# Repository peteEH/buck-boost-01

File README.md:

# buck-boost-01
buck boost programmable regulator - breakout board

- programmable (i2c) buck-boost converter
- 22V in MAX / 20V out MAX - up to 3A out / 4A in
- intention to use as a serially controlled battery charger
- breakout board for the mp28167

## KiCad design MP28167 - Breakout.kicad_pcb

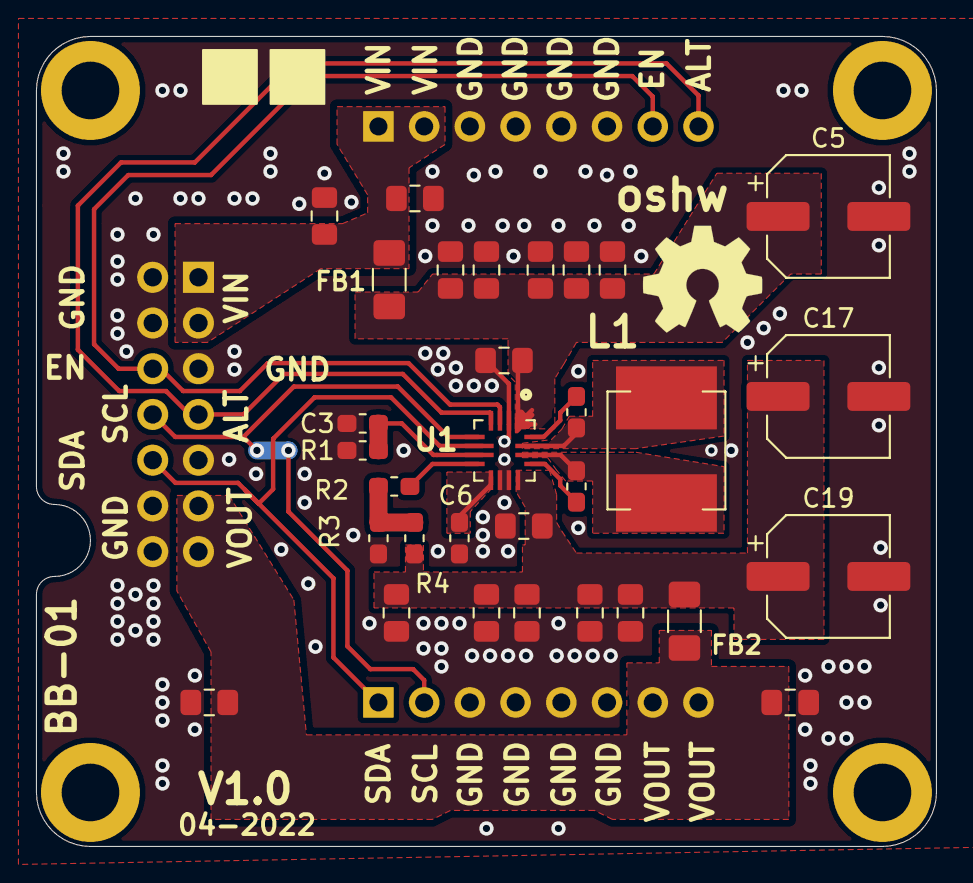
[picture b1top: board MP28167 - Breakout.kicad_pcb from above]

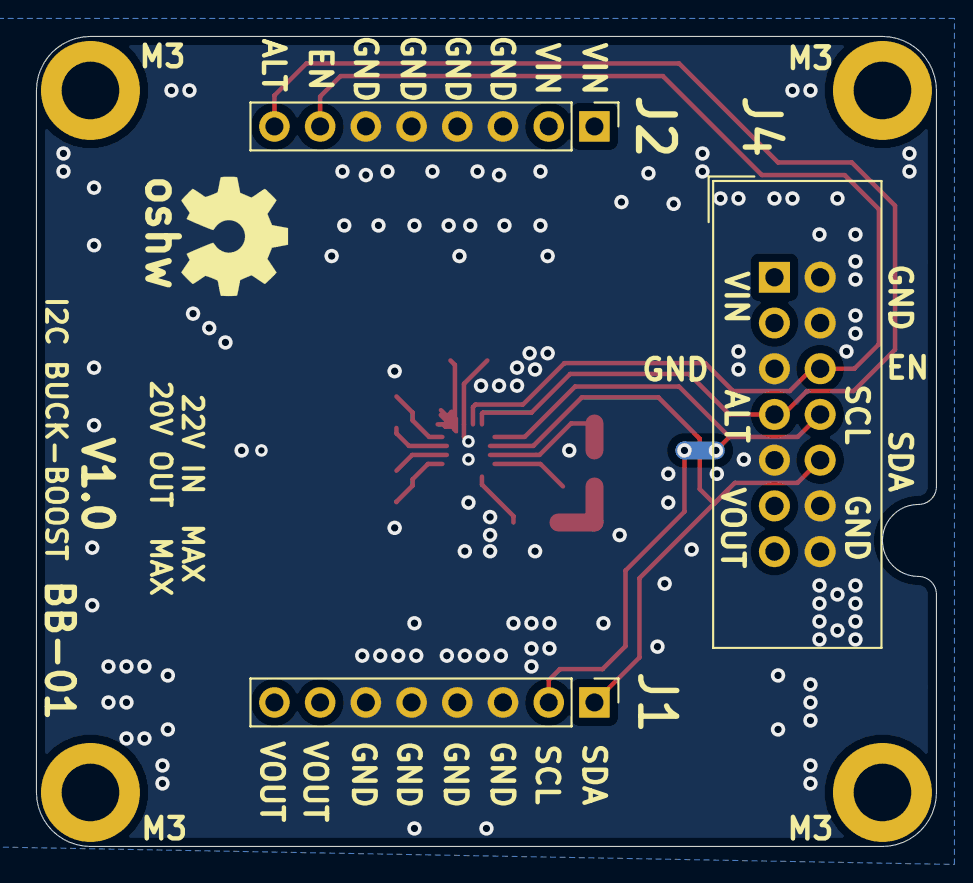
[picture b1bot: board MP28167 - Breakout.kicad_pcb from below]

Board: 2 copper layers, 50.0 x 45.0 mm, 40 parts (4 on the bottom side), 17 nets.

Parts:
C1, C2, C4, C7, C8, C9, C12, C13, C14, C15, C16, C18, C20, C21, C22, C23: 1uF|0805; C_0805_2012Metric_Pad1.15x1.40mm_HandSolder
C3: 22nF|0603; C_0603_1608Metric_Pad1.05x0.95mm_HandSolder
C5, C17, C19: 33uF|35V|6.3D; CP_Elec_6.3x5.4
C6: 1uF|0603; C_0603_1608Metric_Pad1.05x0.95mm_HandSolder
C10, C11: 100nF|0603; C_0603_1608Metric_Pad1.05x0.95mm_HandSolder
FB1, FB2: 4A|1206; L_1206_3216Metric_Pad1.42x1.75mm_HandSolder
H1, H2, H3, H4: M3 Hole; MountingHole_3.2mm_M3_ISO14580_Pad
J1, J2: Conn_01x08; PinHeader_1x08_P2.54mm_Vertical
J4: 2.54mm IDC Header; IDC-Header_2x07_P2.54mm_Vertical
L1: 4.7uF|IHLP2525; L_Vishay_IHLP-2525
LOGO1, LOGO1#2: Logo_Open_Hardware_Large; OSHW-Symbol_6.7x6mm_SilkScreen
R1: 21.5K|0603; R_0603_1608Metric_Pad1.05x0.95mm_HandSolder
R2, R4: 402K|0603; R_0603_1608Metric_Pad1.05x0.95mm_HandSolder
R3: 35.7K|0603; R_0603_1608Metric_Pad1.05x0.95mm_HandSolder
U1: MP28167GQ-A_PH; MP28167GQ-A

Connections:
/BB_FB: R2.2, R3.1, R4.1
/BB_OC: C3.1, R1.1, U1.7
/BB_SW1: C10.1, L1.1, U1.15
/BB_SW2: C11.1, L1.2, U1.14
/BB_VCC: C6.1, U1.9
/BB_VIN_FILT: C2.1, C4.1, C5.1, C7.1, C8.1, C9.1, C12.1, FB1.1, U1.1
/BB_VOUT_FILT: C13.1, C14.1, C15.1, C16.1, C17.1, C18.1, C19.1, C20.1, FB2.2, R4.2, U1.12
ALERT_MPS: J2.8, J4.7, U1.4
BB_VIN: C1.1, C22.1, FB1.2, J2.1, J2.2, J4.1, J4.3
BB_VOUT: C21.1, C23.1, FB2.1, J1.7, J1.8, J4.11, J4.13
GNDREF: C1.2, C2.2, C3.2, C4.2, C5.2, C6.2, C7.2, C8.2, C9.2, C12.2, C13.2, C14.2, C15.2, C16.2, C17.2, C18.2, C19.2, C20.2, C21.2, C22.2, C23.2, J1.3, J1.4, J1.5, J1.6, J2.3, J2.4, J2.5, J2.6, J4.2, J4.4, J4.5, J4.9, J4.12, J4.14, R1.2, R3.2, U1.2, U1.10, U1.11
I2C0_SCL: J1.2, J4.8, U1.5
I2C0_SDA: J1.1, J4.10, U1.6
MPS_EN: J2.7, J4.6, U1.3
unnamed: C10.2, U1.16
unnamed: C11.2, U1.13
unnamed: R2.1, U1.8

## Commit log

2022-04-15 initial set of files
2022-04-16 updated title block

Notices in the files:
parts and their libraries:
Copyright 2021 Accelerated Designs. All rights reserved.
